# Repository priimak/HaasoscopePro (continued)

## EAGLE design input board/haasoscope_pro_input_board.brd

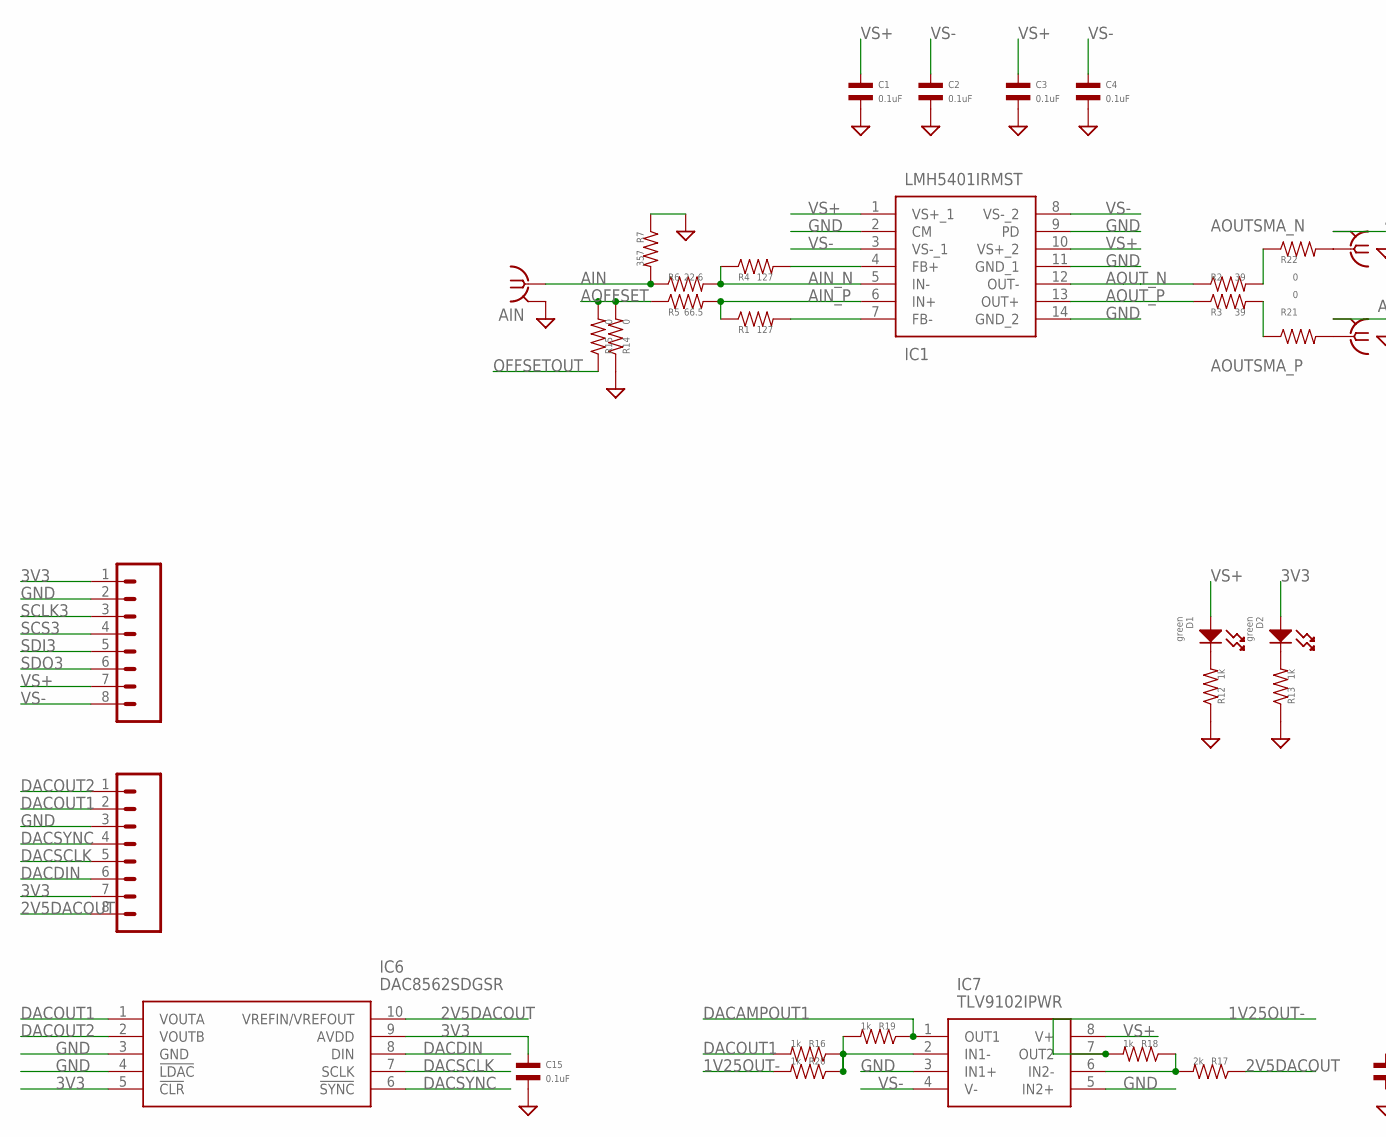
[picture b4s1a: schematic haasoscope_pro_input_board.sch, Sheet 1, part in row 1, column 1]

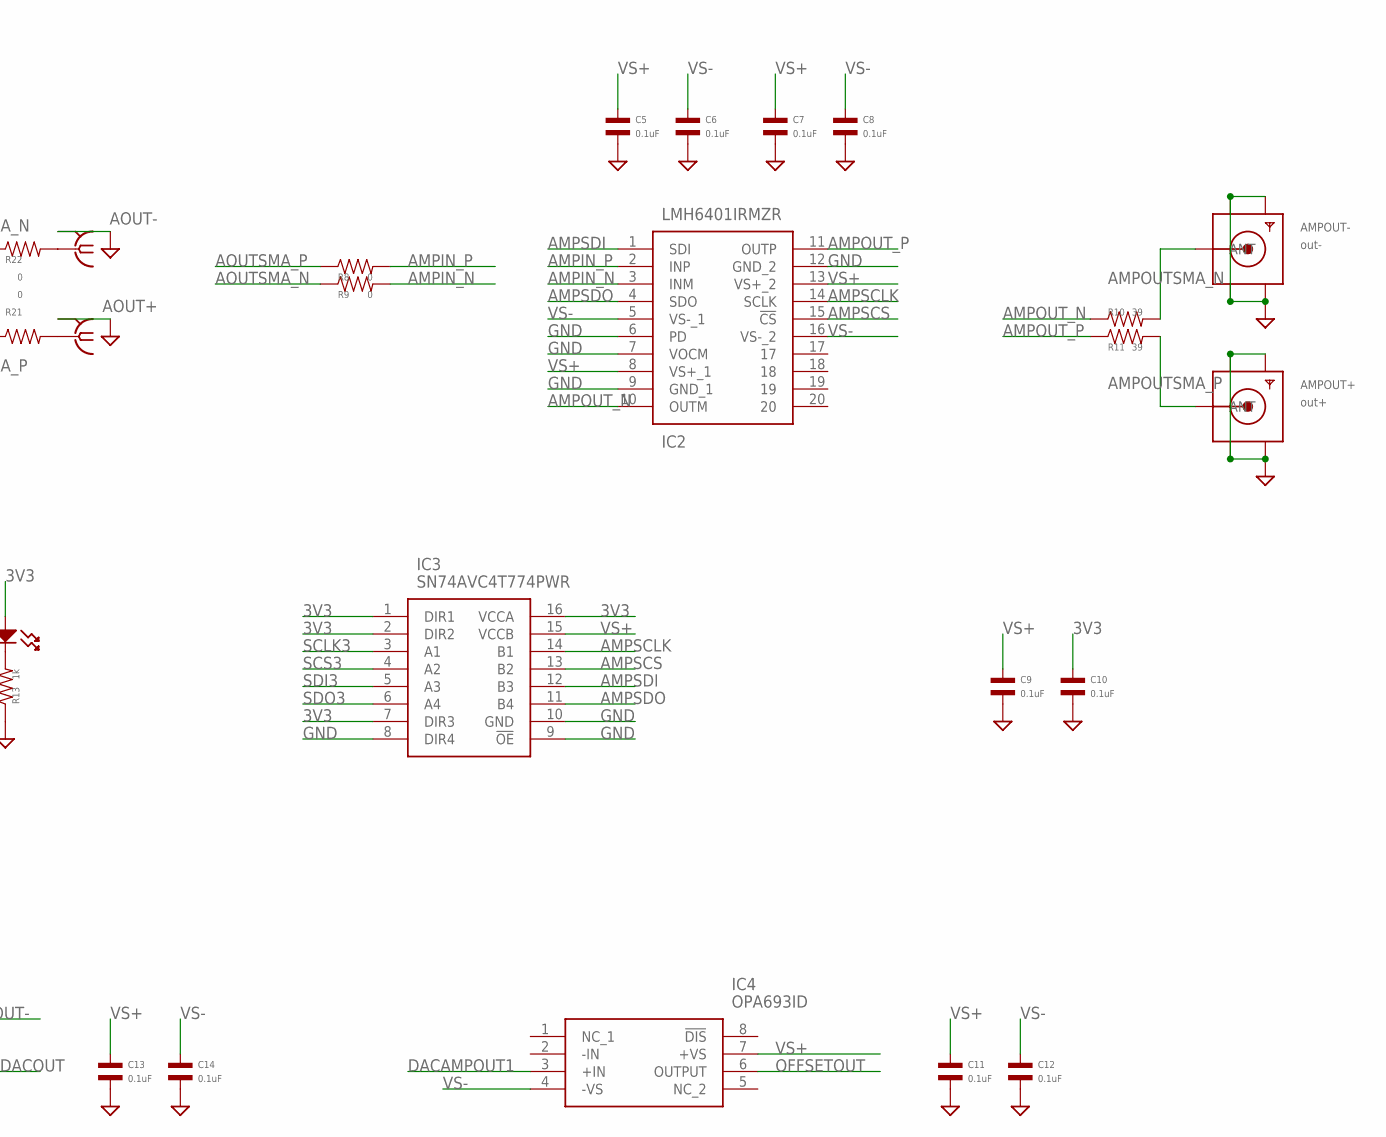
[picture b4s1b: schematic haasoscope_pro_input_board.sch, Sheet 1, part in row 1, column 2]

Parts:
AIN: BU-SMB-V
AMPOUT+: out+; SMA_EDGELAUNCH
AMPOUT-: out-; SMA_EDGELAUNCH
AOUT+: BU-SMB-V
AOUT-: BU-SMB-V
C1, C2, C3, C4, C5, C6, C7, C8, C9, C10, C11, C12, C13, C14, C15: 0.1uF; C0402
D1, D2: green; LED0603
IC1: LMH5401IRMST; LMH5401IRMSR
IC2: LMH6401IRMZR
IC3: SN74AVC4T774PWR; SOP65P640X120-16N
IC4: OPA693ID; SOIC127P600X175-8N
IC6: DAC8562SDGSR; SOP50P490X110-10N
IC7: TLV9102IPWR; SOP65P640X120-8N
J1, J4: 8pin; 1X08
R1, R4: 127; R0402
R2, R3, R10, R11: 39; R0402
R5: 66.5; R0402
R6: 22.6; R0402
R7: 357; R0402
R8, R9, R14, R15, R21, R22: 0; R0402
R12, R13, R16, R18, R19, R20: 1k; R0402
R17: 2k; R0402

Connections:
1V25OUT-: IC7.7 (OUT2), R18.P$2, R20.P$2
2V5DACOUT: IC6.10 (VREFIN/VREFOUT), J1.8, R17.P$1
3V3: C10.P$1, C15.P$1, D2.ANODE, IC3.1 (DIR1), IC3.2 (DIR2), IC3.7 (DIR3), IC3.16 (VCCA), IC6.5 (!CLR), IC6.9 (AVDD), J1.7, J4.1
AIN: AIN.1, R6.P$1, R7.P$2
AIN_N: IC1.5 (IN-), R4.P$1, R6.P$2
AIN_P: IC1.6 (IN+), R1.P$1, R5.P$2
AMPIN_N: IC2.3 (INM), R9.P$2
AMPIN_P: IC2.2 (INP), R8.P$2
AMPOUTSMA_N: AMPOUT-.P (ANT), R10.P$2
AMPOUTSMA_P: AMPOUT+.P (ANT), R11.P$2
AMPOUT_N: IC2.10 (OUTM), R10.P$1
AMPOUT_P: IC2.11 (OUTP), R11.P$1
AMPSCLK: IC2.14 (SCLK), IC3.14 (B1)
AMPSCS: IC2.15 (!CS), IC3.13 (B2)
AMPSDI: IC2.1 (SDI), IC3.12 (B3)
AMPSDO: IC2.4 (SDO), IC3.11 (B4)
AOFFSET: R5.P$1, R14.P$2, R15.P$2
AOUTSMA_N: R2.P$2, R9.P$1, R22.P$1
AOUTSMA_P: R3.P$2, R8.P$1, R21.P$1
AOUT_N: IC1.12 (OUT-), R2.P$1
AOUT_P: IC1.13 (OUT+), R3.P$1
DACAMPOUT1: IC4.3 (+IN), IC7.1 (OUT1), R19.P$1
DACDIN: IC6.8 (DIN), J1.6
DACOUT1: IC6.1 (VOUTA), J1.2, R16.P$2
DACOUT2: IC6.2 (VOUTB), J1.1
DACSCLK: IC6.7 (SCLK), J1.5
DACSYNC: IC6.6 (!SYNC), J1.4
GND: AIN.2, AIN.3 (2), AIN.4 (2), AIN.5 (2), AMPOUT+.GND@1 (GND4), AMPOUT+.GND@2 (GND3), AMPOUT+.GND@3 (GND2), AMPOUT+.GND@4 (GND1), AMPOUT-.GND@1 (GND4), AMPOUT-.GND@2 (GND3), AMPOUT-.GND@3 (GND2), AMPOUT-.GND@4 (GND1), AOUT+.2, AOUT+.3 (2), AOUT+.4 (2), AOUT+.5 (2), AOUT-.2, AOUT-.3 (2), AOUT-.4 (2), AOUT-.5 (2), C1.P$2, C2.P$2, C3.P$2, C4.P$2, C5.P$2, C6.P$2, C7.P$2, C8.P$2, C9.P$2, C10.P$2, C11.P$2, C12.P$2, C13.P$2, C14.P$2, C15.P$2, IC1.2 (CM), IC1.9 (PD), IC1.11 (GND_1), IC1.14 (GND_2), IC2.6 (PD), IC2.7 (VOCM), IC2.9 (GND_1), IC2.12 (GND_2), IC3.8 (DIR4), IC3.9 (!OE), IC3.10 (GND), IC6.3 (GND), IC6.4 (!LDAC), IC7.3 (IN1+), IC7.5 (IN2+), J1.3, J4.2, R7.P$1, R12.P$1, R13.P$1, R14.P$1
unnamed: D1.CATHODE, R12.P$2
unnamed: D2.CATHODE, R13.P$2
unnamed: IC7.2 (IN1-), R16.P$1, R19.P$2, R20.P$1
unnamed: AOUT-.1, R22.P$2
unnamed: IC7.6 (IN2-), R17.P$2, R18.P$1
unnamed: AOUT+.1, R21.P$2
unnamed: IC1.7 (FB-), R1.P$2
unnamed: IC1.4 (FB+), R4.P$2
OFFSETOUT: IC4.6 (OUTPUT), R15.P$1
SCLK3: IC3.3 (A1), J4.3
SCS3: IC3.4 (A2), J4.4
SDI3: IC3.5 (A3), J4.5
SDO3: IC3.6 (A4), J4.6
VS+: C1.P$1, C3.P$1, C5.P$1, C7.P$1, C9.P$1, C11.P$1, C13.P$1, D1.ANODE, IC1.1 (VS+_1), IC1.10 (VS+_2), IC2.8 (VS+_1), IC2.13 (VS+_2), IC3.15 (VCCB), IC4.7 (+VS), IC7.8 (V+), J4.7
VS-: C2.P$1, C4.P$1, C6.P$1, C8.P$1, C12.P$1, C14.P$1, IC1.3 (VS-_1), IC1.8 (VS-_2), IC2.5 (VS-_1), IC2.16 (VS-_2), IC4.4 (-VS), IC7.4 (V-), J4.8

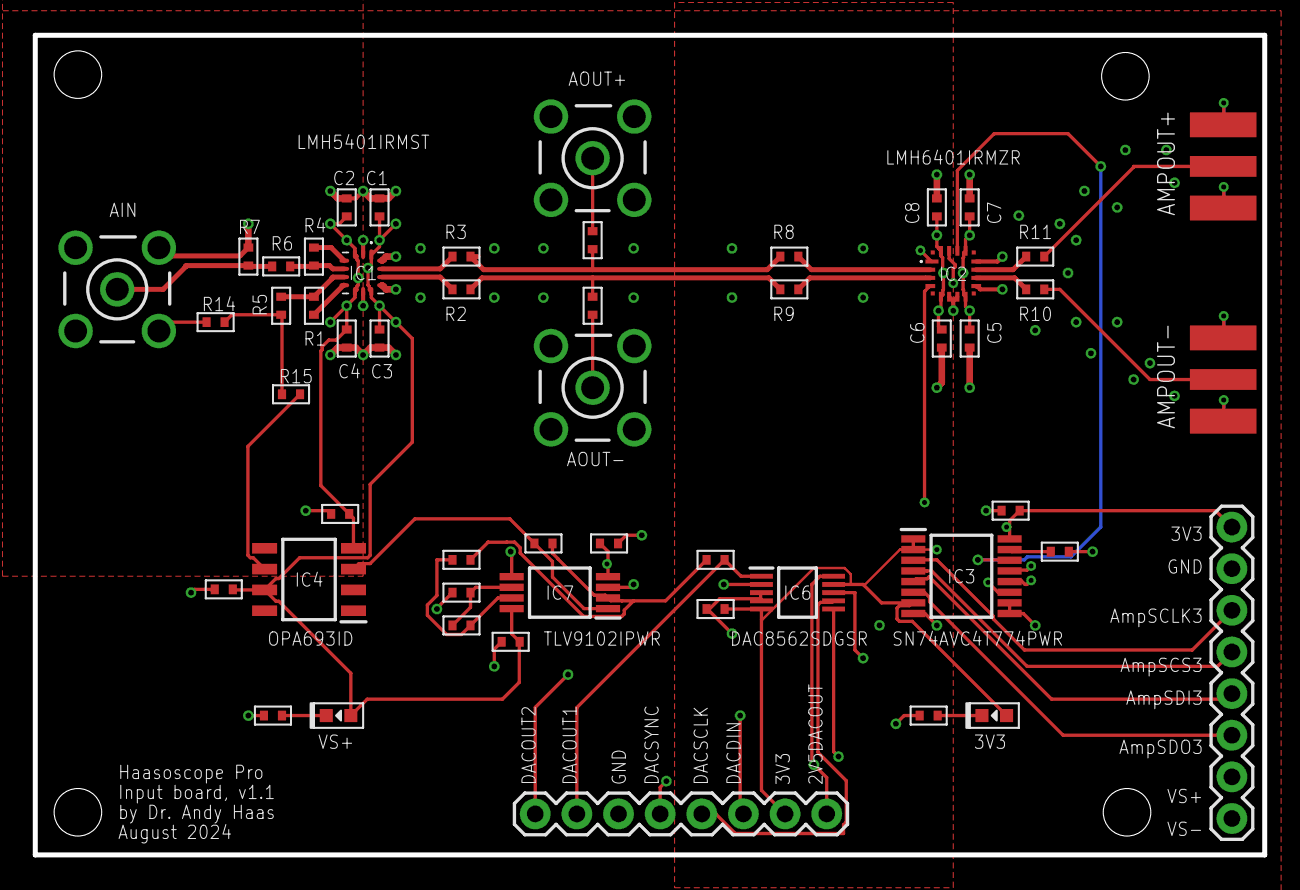
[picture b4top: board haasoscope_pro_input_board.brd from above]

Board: 4 copper layers, 75.0 x 50.0 mm, 52 parts (0 on the bottom side), 43 nets.

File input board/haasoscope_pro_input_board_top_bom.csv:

Comment,Designator,Footprint,LCSC Part #
0,AMPOUT+ AMPOUT- R8 R9 R14 R15 R21 R22,R0402,
0.1uF,C1 C2 C3 C4 C5 C6 C7 C8 C9 C10 C11 C12 C13 C14 C15,C0402,
1k,R12 R13 R16 R18 R19 R20,R0402,
2k,R17,R0402,
22.6,R6,R0402,
39,R2 R3 R10 R11,R0402,
66.5,R5,R0402,
127,R1 R4,R0402,
357,R7,R0402,
DAC8562SDGSR,IC6,SOP50P490X110-10N,
LMH5401IRMST,IC1,LMH5401IRMSR,
LMH6401IRMZR,IC2,LMH6401IRMZR,
OPA693ID,IC4,SOIC127P600X175-8N,
SN74AVC4T774PWR,IC3,SOP65P640X120-16N,
TLV9102IPWR,IC7,SOP65P640X120-8N,
green,D1 D2,LED0603,
